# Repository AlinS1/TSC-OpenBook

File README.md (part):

# OpenBook Project - TSC
### Similea Alin-Andrei 334CA

## Diagrama

## Descriere functionalitate hardware
Dispozitivul are in centrul sau un microcontroler ESP32-C6 care interactioneaza cu
un display, un senzor de mediu, un RTC, un SD card si un circuit de gestionare a
alimentarii. Este un dispozitiv alimentat cu baterie, cu conectivitate USB-C.

In ceea ce priveste alimentarea dispozitivului, se foloseste conectorul USB-C
(SAMACSYS_PARTS_USB4110-GF-A) ce dispune de protectie ESD.
Are un controller de incarcare pentru baterii Li-Po(Li-Po Battery Charging
Controller - MCP73831) care se ocupa de incarcarea bateriei.
Mai exista si un stabilizator de tensiune LDO Voltage Regulator (XC6220A331MR-G)
ce asigura o alimentare stabila.
Nivelul de incarcare al bateriei este monitorizat cu ajutorul Battery Charge
Level (MAX17048G+T).

In ceea ce priveste memoria, este inclus un slot pentru card SD
(112A-TAAR-R03_ATTEND). In plus, avem o memorie Flash NOR externa (W25Q512JVIQ)
cu o capacitate de 64MB. Comunicarea cu acestea se face prin SPI (avem MOSI,
MISO, SS_SD si SCK).

Modulul DS3231SN RTC este responsabil pentru mentinerea timpului.
Comunicarea cu controller-ul se face prin I2C (deoarece avem SDA si SCL).
Dispozitivul are integrat si un senzor BME680, destinat analizei aerului,
masurarea presiunii atmosferice, temperaturii si umiditatii. Comunicare cu ESP32
se face tot prin I2C.
Este prezent o componenta Qwiic (QWIIC_CONNECTORJS-1MM) ce ne ajuta sa conectam
usor componente I2C intre ele. 

## Pini ESP32-C6
Modulul DS3231SN RTC foloseste pinii lui ESP32-C6 pentru SDA(19) si SCL(20),
deoarece comunica prin I2C. SDA e folosit pentru transferul de date, iar SCL
este linia de ceas folosita la sincronizare.

Senzorul de mediu BME680 foloseste aceiasi pini ca modulul RTC din aceleasi motive.

Cardul SD foloseste MOSI(7), MISO(27), SS_SD(4) si SCK(6), deoarece comunica prin SPI.

Display-ul E-Paper foloseste pini speciali ca EPD_3V3_C(18), EPD_CS(11), EPD_DC(5),
EPD_RST(21), EPD_BUSY(26).

Butoanele folosesc pinii RESET(3), IO/BOOT(15) si IO/CHANGE(23) pentru a realiza anumite actiuni.

## Rezolvare Erori/Warnings

De-alungul implementarii am avut urmatoarele probleme:
1. Bobina L1 - "Copper Width error" - a trebuit sa modific dimensiunile pad-urilor
din biblioteca data, deoarece nu erau conforme cu DRC-ul.

2. Componenta U4 - "Smd, -Net Class: 1 POWER Top" - Modificam dimensiunea smd-urilor
vizate la 32mil x 16mil.

3. Pentru ca traseele de alimentare sa aiba width (0.3mm) diferit de celelalte
(0.15mm) vom crea o regula custom pentru Copper Width folosind un net class separat
ce contine label-urile destinate traseelor de alimentare.

4. Pentru a ne asigura ca evitam vias-urile la traseele de putere, vom face prima
data rutarea acestora cu ajutorul liniei de comanda.
(auto 3V3 EPD_3V3 EPD_3V3_C VBUS VUSB VBAT VRTC)

## Bill Of Materials

| Schematic name | Value | Component | Footprint Name | Component link | Datasheet link |
|----------------|----------|----------------|----------------|----------------|----------------|		
|	BOOT_BUTTON	|	BUTTON_CUSYOMV1	|	BUTTON_CUSYOMV1	|	MYBUTTON	|	https://industry.panasonic.com/global/en/products/control/switch/light-touch/number/evqpuj02k	|	https://industry.panasonic.com/global/en/downloads?tab=catalog&small_g_cd=203&part_no=EVQPUJ02K	|
|	C1	|	100nF	|	ESP32_WROVER_EAGLE-LTSPICE_CC0402	|	ESP32_WROVER_EAGLE-LTSPICE_C0402	|	https://componentsearchengine.com/part-view/CC0402MRX5R5BB106/YAGEO	|	https://componentsearchengine.com/Datasheets/2/CC0402MRX5R5BB106.pdf	|
|	C1_BAT	|	4.7uF	|	ESP32_WROVER_EAGLE-LTSPICE_CC0402	|	ESP32_WROVER_EAGLE-LTSPICE_C0402	|	https://componentsearchengine.com/part-view/CC0402MRX5R5BB106/YAGEO	|	https://componentsearchengine.com/Datasheets/2/CC0402MRX5R5BB106.pdf	|
|	C1_BAT1	|	4.7uF	|	EAGLE-LTSPICE_CC0402	|	EAGLE-LTSPICE_C0402	|	https://www.snapeda.com/parts/CC0402DRNPO9BN5R1/Yageo/view-part/?ref=dk&t=LTSPICE_CC0402&con_ref=None	|	https://s3.amazonaws.com/snapeda/datasheet/CC0402DRNPO9BN5R1_Yageo.pdf	|
|	C2_BAT1	|	4.7uF	|	EAGLE-LTSPICE_CC0402	|	EAGLE-LTSPICE_C0402	|	https://www.snapeda.com/parts/CC0402DRNPO9BN5R1/Yageo/view-part/?ref=dk&t=LTSPICE_CC0402&con_ref=None	|	https://s3.amazonaws.com/snapeda/datasheet/CC0402DRNPO9BN5R1_Yageo.pdf	|
|	C1_BAT2	|	4.7uF	|	EAGLE-LTSPICE_CC0402	|	EAGLE-LTSPICE_C0402	|	https://www.snapeda.com/parts/CC0402DRNPO9BN5R1/Yageo/view-part/?ref=dk&t=LTSPICE_CC0402&con_ref=None	|	https://s3.amazonaws.com/snapeda/datasheet/CC0402DRNPO9BN5R1_Yageo.pdf	|
|	C2	|	100nF	|	ESP32_WROVER_EAGLE-LTSPICE_CC0402	|	ESP32_WROVER_EAGLE-LTSPICE_C0402	|	https://componentsearchengine.com/part-view/CC0402MRX5R5BB106/YAGEO	|	https://componentsearchengine.com/Datasheets/2/CC0402MRX5R5BB106.pdf	|
|	C2_BAT	|	4.7uF	|	ESP32_WROVER_EAGLE-LTSPICE_CC0402	|	ESP32_WROVER_EAGLE-LTSPICE_C0402	|	https://componentsearchengine.com/part-view/CC0402MRX5R5BB106/YAGEO	|	https://componentsearchengine.com/Datasheets/2/CC0402MRX5R5BB106.pdf	|
|	C3	|	100uF TANT	|	RCL_CPOL-EUCT3528	|	RCL_CT3528	|	https://www.snapeda.com/parts/TAJB475K025RNJ/AVX/view-part/?ref=dk&t=capacitor%203528&con_ref=None	|	https://s3.amazonaws.com/snapeda/datasheet/TAJB475K025RNJ_AVX.pdf	|
|	C4	|	4.7uF/25V	|	ESP32_WROVER_EAGLE-LTSPICE_CC0402	|	ESP32_WROVER_EAGLE-LTSPICE_C0402	|	https://componentsearchengine.com/part-view/CC0402MRX5R5BB106/YAGEO	|	https://componentsearchengine.com/Datasheets/2/CC0402MRX5R5BB106.pdf	|
|	C4_USB	|	100nF	|	ESP32_WROVER_EAGLE-LTSPICE_CC0402	|	ESP32_WROVER_EAGLE-LTSPICE_C0402	|	https://componentsearchengine.com/part-view/CC0402MRX5R5BB106/YAGEO	|	https://componentsearchengine.com/Datasheets/2/CC0402MRX5R5BB106.pdf	|
|	C5	|	1uF	|	ESP32_WROVER_EAGLE-LTSPICE_CC0402	|	ESP32_WROVER_EAGLE-LTSPICE_C0402	|	https://componentsearchengine.com/part-view/CC0402MRX5R5BB106/YAGEO	|	https://componentsearchengine.com/Datasheets/2/CC0402MRX5R5BB106.pdf	|
|	C5_USB	|	4.7uF	|	ESP32_WROVER_EAGLE-LTSPICE_CC0402	|	ESP32_WROVER_EAGLE-LTSPICE_C0402	|	https://componentsearchengine.com/part-view/CC0402MRX5R5BB106/YAGEO	|	https://componentsearchengine.com/Datasheets/2/CC0402MRX5R5BB106.pdf	|
|	C6	|	100nF	|	ESP32_WROVER_EAGLE-LTSPICE_CC0402	|	ESP32_WROVER_EAGLE-LTSPICE_C0402	|	https://componentsearchengine.com/part-view/CC0402MRX5R5BB106/YAGEO	|	https://componentsearchengine.com/Datasheets/2/CC0402MRX5R5BB106.pdf	|
|	C7	|	10uF	|	ESP32_WROVER_EAGLE-LTSPICE_CC0402	|	ESP32_WROVER_EAGLE-LTSPICE_C0402	|	https://componentsearchengine.com/part-view/CC0402MRX5R5BB106/YAGEO	|	https://componentsearchengine.com/Datasheets/2/CC0402MRX5R5BB106.pdf	|
|	C8	|	100nF	|	ESP32_WROVER_EAGLE-LTSPICE_CC0402	|	ESP32_WROVER_EAGLE-LTSPICE_C0402	|	https://componentsearchengine.com/part-view/CC0402MRX5R5BB106/YAGEO	|	https://componentsearchengine.com/Datasheets/2/CC0402MRX5R5BB106.pdf	|
|	C9	|	100nF	|	EAGLE-LTSPICE_CC0402	|	EAGLE-LTSPICE_C0402	|	https://www.snapeda.com/parts/CC0402DRNPO9BN5R1/Yageo/view-part/?ref=dk&t=LTSPICE_CC0402&con_ref=None	|	https://s3.amazonaws.com/snapeda/datasheet/CC0402DRNPO9BN5R1_Yageo.pdf	|
|	C10	|	100nF	|	ESP32_WROVER_EAGLE-LTSPICE_CC0402	|	ESP32_WROVER_EAGLE-LTSPICE_C0402	|	https://componentsearchengine.com/part-view/CC0402MRX5R5BB106/YAGEO	|	https://componentsearchengine.com/Datasheets/2/CC0402MRX5R5BB106.pdf	|
|	C10_SUPERCAP	|	CPH3225A	|	CPH3225A	|	CAPCP3225X100N	|	https://www.snapeda.com/parts/CPH3225A/Seiko+Instruments/view-part/?ref=eda	|	https://www.snapeda.com/parts/CPH3225A/Seiko%20Instruments/datasheet/	|
|	CHANGE_BUTTON	|	BUTTON_CUSYOMV1	|	BUTTON_CUSYOMV1	|	MYBUTTON	|	https://industry.panasonic.com/global/en/products/control/switch/light-touch/number/evqpuj02k	|	https://industry.panasonic.com/global/en/downloads?tab=catalog&small_g_cd=203&part_no=EVQPUJ02K	|
|	CHG_LED	|		|	ADAFRUIT_LEDCHIP-LED0603	|	ADAFRUIT_CHIP-LED0603	|	https://www.snapeda.com/parts/KP-1608SURCK/Kingbright/view-part/?ref=search&t=LED%200603	|	https://www.snapeda.com/parts/KP-1608SURCK/Kingbright/datasheet/	|
|	C_DELAY	|	100nF	|	ESP32_WROVER_EAGLE-LTSPICE_CC0402	|	ESP32_WROVER_EAGLE-LTSPICE_C0402	|	https://componentsearchengine.com/part-view/CC0402MRX5R5BB106/YAGEO	|	https://componentsearchengine.com/Datasheets/2/CC0402MRX5R5BB106.pdf	|
|	D1	|	USBLC6-2SC6Y	|	USBLC6-2SC6Y	|	SOT95P280X145-6N	|	https://www.snapeda.com/parts/USBLC6-2SC6Y/STMicroelectronics/view-part/?ref=snap	|	https://www.snapeda.com/parts/USBLC6-2SC6Y/STMicroelectronics/datasheet/	|
|	D2	|	ESP32_WROVER_AVX---SD0805S020S1R0_AVX_SD0805S020S1R0_0_0AVX_SD0805S020S1R0_0_0	|	ESP32_WROVER_AVX---SD0805S020S1R0_AVX_SD0805S020S1R0_0_0AVX_SD0805S020S1R0_0_0	|	ESP32_WROVER_AVX---SD0805S020S1R0_AVX_SD0805S020S1R0_0	|	https://ro.mouser.com/ProductDetail/KYOCERA-AVX/SD0805S020S1R0?qs=jCA%252BPfw4LHbpkAoSnwrdjw%3D%3D	|	http://datasheets.avx.com/schottky.pdf	|
|	D3	|	MBR0530	|	MBR0530	|	SOD3716X135N	|	https://www.snapeda.com/parts/MBR0530/Onsemi/view-part/?ref=eda	|	https://www.snapeda.com/parts/MBR0530/ON%20Semiconductor/datasheet/	|
|	D4	|	MBR0530	|	MBR0530	|	SOD3716X135N	|	https://www.snapeda.com/parts/MBR0530/Onsemi/view-part/?ref=eda	|	https://www.snapeda.com/parts/MBR0530/ON%20Semiconductor/datasheet/	|
|	D5	|	MBR0530	|	MBR0530	|	SOD3716X135N	|	https://www.snapeda.com/parts/MBR0530/Onsemi/view-part/?ref=eda	|	https://www.snapeda.com/parts/MBR0530/ON%20Semiconductor/datasheet/	|
|	D6	|	PGB1010603MR	|	PGB1010603MR	|	DIOC1608X36N	|	https://www.snapeda.com/parts/PGB1010603MR/Littelfuse/view-part/?ref=eda	|	https://www.snapeda.com/parts/PGB1010603MR/Littelfuse%20Inc./datasheet/	|
|	D7	|	ESP32_WROVER_AVX---SD0805S020S1R0_AVX_SD0805S020S1R0_0_0AVX_SD0805S020S1R0_0_0	|	ESP32_WROVER_AVX---SD0805S020S1R0_AVX_SD0805S020S1R0_0_0AVX_SD0805S020S1R0_0_0	|	ESP32_WROVER_AVX---SD0805S020S1R0_AVX_SD0805S020S1R0_0	|	https://eu.mouser.com/ProductDetail/KYOCERA-AVX/SD0805S020S1R0?qs=jCA%252BPfw4LHbpkAoSnwrdjw%3D%3D	|	http://datasheets.avx.com/schottky.pdf	|
|	D8	|	PGB1010603MR	|	PGB1010603MR	|	DIOC1608X36N	|	https://www.snapeda.com/parts/PGB1010603MR/Littelfuse/view-part/?ref=eda	|	https://www.snapeda.com/parts/PGB1010603MR/Littelfuse%20Inc./datasheet/	|
|	D9	|	PGB1010603MR	|	PGB1010603MR	|	DIOC1608X36N	|	https://www.snapeda.com/parts/PGB1010603MR/Littelfuse/view-part/?ref=eda	|	https://www.snapeda.com/parts/PGB1010603MR/Littelfuse%20Inc./datasheet/	|
|	D10	|	PGB1010603MR	|	PGB1010603MR	|	DIOC1608X36N	|	https://www.snapeda.com/parts/PGB1010603MR/Littelfuse/view-part/?ref=eda	|	https://www.snapeda.com/parts/PGB1010603MR/Littelfuse%20Inc./datasheet/	|
|	D11	|	PGB1010603MR	|	PGB1010603MR	|	DIOC1608X36N	|	https://www.snapeda.com/parts/PGB1010603MR/Littelfuse/view-part/?ref=eda	|	https://www.snapeda.com/parts/PGB1010603MR/Littelfuse%20Inc./datasheet/	|
|	D12	|	PGB1010603MR	|	PGB1010603MR	|	DIOC1608X36N	|	https://www.snapeda.com/parts/PGB1010603MR/Littelfuse/view-part/?ref=eda	|	https://www.snapeda.com/parts/PGB1010603MR/Littelfuse%20Inc./datasheet/	|
|	EPD_C1	|	1uF/50V	|	ESP32_WROVER_EAGLE-LTSPICE_CC0402	|	ESP32_WROVER_EAGLE-LTSPICE_C0402	|	https://componentsearchengine.com/part-view/CC0402MRX5R5BB106/YAGEO	|	https://componentsearchengine.com/Datasheets/2/CC0402MRX5R5BB106.pdf	|
|	EPD_C2	|	1uF/50V	|	ESP32_WROVER_EAGLE-LTSPICE_CC0402	|	ESP32_WROVER_EAGLE-LTSPICE_C0402	|	https://componentsearchengine.com/part-view/CC0402MRX5R5BB106/YAGEO	|	https://componentsearchengine.com/Datasheets/2/CC0402MRX5R5BB106.pdf	|
|	EPD_C5	|	1uF/50V	|	ESP32_WROVER_EAGLE-LTSPICE_CC0402	|	ESP32_WROVER_EAGLE-LTSPICE_C0402	|	https://componentsearchengine.com/part-view/CC0402MRX5R5BB106/YAGEO	|	https://componentsearchengine.com/Datasheets/2/CC0402MRX5R5BB106.pdf	|
|	EPD_C6	|	1uF/50V	|	ESP32_WROVER_EAGLE-LTSPICE_CC0402	|	ESP32_WROVER_EAGLE-LTSPICE_C0402	|	https://componentsearchengine.com/part-view/CC0402MRX5R5BB106/YAGEO	|	https://componentsearchengine.com/Datasheets/2/CC0402MRX5R5BB106.pdf	|
|	EPD_C7	|	1uF/50V	|	ESP32_WROVER_EAGLE-LTSPICE_CC0402	|	ESP32_WROVER_EAGLE-LTSPICE_C0402	|	https://componentsearchengine.com/part-view/CC0402MRX5R5BB106/YAGEO	|	https://componentsearchengine.com/Datasheets/2/CC0402MRX5R5BB106.pdf	|
|	EPD_C8	|	1uF/50V	|	ESP32_WROVER_EAGLE-LTSPICE_CC0402	|	ESP32_WROVER_EAGLE-LTSPICE_C0402	|	https://componentsearchengine.com/part-view/CC0402MRX5R5BB106/YAGEO	|	https://componentsearchengine.com/Datasheets/2/CC0402MRX5R5BB106.pdf	|
|	EPD_C9	|	1uF/50V	|	ESP32_WROVER_EAGLE-LTSPICE_CC0402	|	ESP32_WROVER_EAGLE-LTSPICE_C0402	|	https://componentsearchengine.com/part-view/CC0402MRX5R5BB106/YAGEO	|	https://componentsearchengine.com/Datasheets/2/CC0402MRX5R5BB106.pdf	|
|	EPD_C10	|	1uF/50V	|	ESP32_WROVER_EAGLE-LTSPICE_CC0402	|	ESP32_WROVER_EAGLE-LTSPICE_C0402	|	https://componentsearchengine.com/part-view/CC0402MRX5R5BB106/YAGEO	|	https://componentsearchengine.com/Datasheets/2/CC0402MRX5R5BB106.pdf	|
|	EPD_C11	|	1uF/50V	|	ESP32_WROVER_EAGLE-LTSPICE_CC0402	|	ESP32_WROVER_EAGLE-LTSPICE_C0402	|	https://componentsearchengine.com/part-view/CC0402MRX5R5BB106/YAGEO	|	https://componentsearchengine.com/Datasheets/2/CC0402MRX5R5BB106.pdf	|
|	EPD_C12	|	1uF/50V	|	ESP32_WROVER_EAGLE-LTSPICE_CC0402	|	ESP32_WROVER_EAGLE-LTSPICE_C0402	|	https://componentsearchengine.com/part-view/CC0402MRX5R5BB106/YAGEO	|	https://componentsearchengine.com/Datasheets/2/CC0402MRX5R5BB106.pdf	|
|	IC1	|	BD5229G-TR	|	BD5229G-TR	|	SOT95P280X125-5N	|	https://componentsearchengine.com/part-view/BD5229G-TR/ROHM%20Semiconductor	|	https://datasheet.datasheetarchive.com/originals/distributors/Datasheets_SAMA/f2b9741ef86007909f138d561a359946.pdf	|
|	IC4	|	XC6220A331MR-G	|	XC6220A331MR-G	|	SOT95P280X120-5N	|	https://componentsearchengine.com/part-view/XC6220A331MR-G/Torex	|	https://product.torexsemi.com/system/files/series/xc6220.pdf	|
|	J1	|	FH34SRJ-24S-0.5SH_99_	|	FH34SRJ-24S-0.5SH_99_	|	FH34SRJ24S05SH99	|	https://componentsearchengine.com/part-view/FH34SRJ-24S-0.5SH(99)/Hirose	|	https://www.hirose.com/en/product/document?clcode=CL0580-1255-6-99&productname=FH34SRJ-24S-0.5SH(99)&series=FH34SRJ&documenttype=2DDrawing&lang=en&documentid=0000990903	|
|	J2	|	SAMACSYS_PARTS_USB4110-GF-A	|	SAMACSYS_PARTS_USB4110-GF-A	|	SAMACSYS_PARTS_USB4110GFA	|	https://componentsearchengine.com/part-view/USB4110-GF-A/GCT%20(GLOBAL%20CONNECTOR%20TECHNOLOGY)	|	https://gct.co/files/drawings/usb4110.pdf	|
|	J3	|	QWIIC_RIGHT_ANGLE	|	QWIIC_CONNECTORJS-1MM	|	JST04_1MM_RA	|	https://grabcad.com/library/sparkfun-qwiic-right-angle-1	|	https://eu.mouser.com/ProductDetail/Adafruit/4208?qs=PzGy0jfpSMtbScLbr0L5dw%3D%3D	|
|	J4	|	112A-TAAR-R03_ATTEND	|	112A-TAAR-R03_ATTEND	|	112ATAARR03ATTEND	|	https://store.comet.srl.ro/Catalogue/Product/43497/	|	https://store.comet.srl.ro/Catalogue/Product/43497/	|
|	L1	|	68uH	|	744043680IND_4828-WE-TPC_WRE	|	IND_4828-WE-TPC_WRE	|	https://ro.mouser.com/ProductDetail/Wurth-Elektronik/744043680?qs=PGXP4M47uW6VkZq%252BkzjrHA%3D%3D	|	https://www.we-online.com/components/products/datasheet/744043680.pdf	|
|	PFMF.050.1	|	ESP32C6_VARISTORCN1812	|	ESP32C6_VARISTORCN1812	|	ESP32C6_VARISTOR_CT/CN1812	|	https://www.mouser.co.uk/ProductDetail/EPCOS-TDK/B72520T0350K062?qs=dEfas%2FXlABIszF52uu7vrg%3D%3D	|	https://www.mouser.co.uk/ProductDetail/EPCOS-TDK/B72520T0350K062?qs=dEfas%2FXlABIszF52uu7vrg%3D%3D	|
|	Q1	|	20V/4.2A/52mO/1.4W	|	ESP32_WROVER_SPARKFUN-DISCRETESEMI_MOSFET_PCH-DMG2305UX-7	|	ESP32_WROVER_SPARKFUN-DISCRETESEMI_SOT23-3	|	https://componentsearchengine.com/part-view/DMG2305UX-7/Diodes%20Incorporated	|	https://www.diodes.com//assets/Datasheets/DMG2305UX.pdf	|
|	Q2	|	20V/4.2A/52mO/1.4W	|	ESP32_WROVER_SPARKFUN-DISCRETESEMI_MOSFET_PCH-DMG2305UX-7	|	ESP32_WROVER_SPARKFUN-DISCRETESEMI_SOT23-3	|	https://componentsearchengine.com/part-view/DMG2305UX-7/Diodes%20Incorporated	|	https://www.diodes.com//assets/Datasheets/DMG2305UX.pdf	|
|	Q3	|	SI1308EDL-T1-GE3	|	D8	|	SOT65P210X110-3N	|	https://componentsearchengine.com/part-view/SI1308EDL-T1-GE3/Vishay	|	https://componentsearchengine.com/Datasheets/1/SI1308EDL-T1-GE3.pdf	|
|	R1	|	10K	|	ESP32_WROVER_EAGLE-LTSPICE_RR0402	|	ESP32_WROVER_EAGLE-LTSPICE_R0402	|	https://componentsearchengine.com/part-view/R0402%201%25%20100%20K%20(RC0402FR-07100KL)/YAGEO	|	https://www.yageo.com/upload/media/product/products/datasheet/rchip/PYu-RC_Group_51_RoHS_L_12.pdf	|
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
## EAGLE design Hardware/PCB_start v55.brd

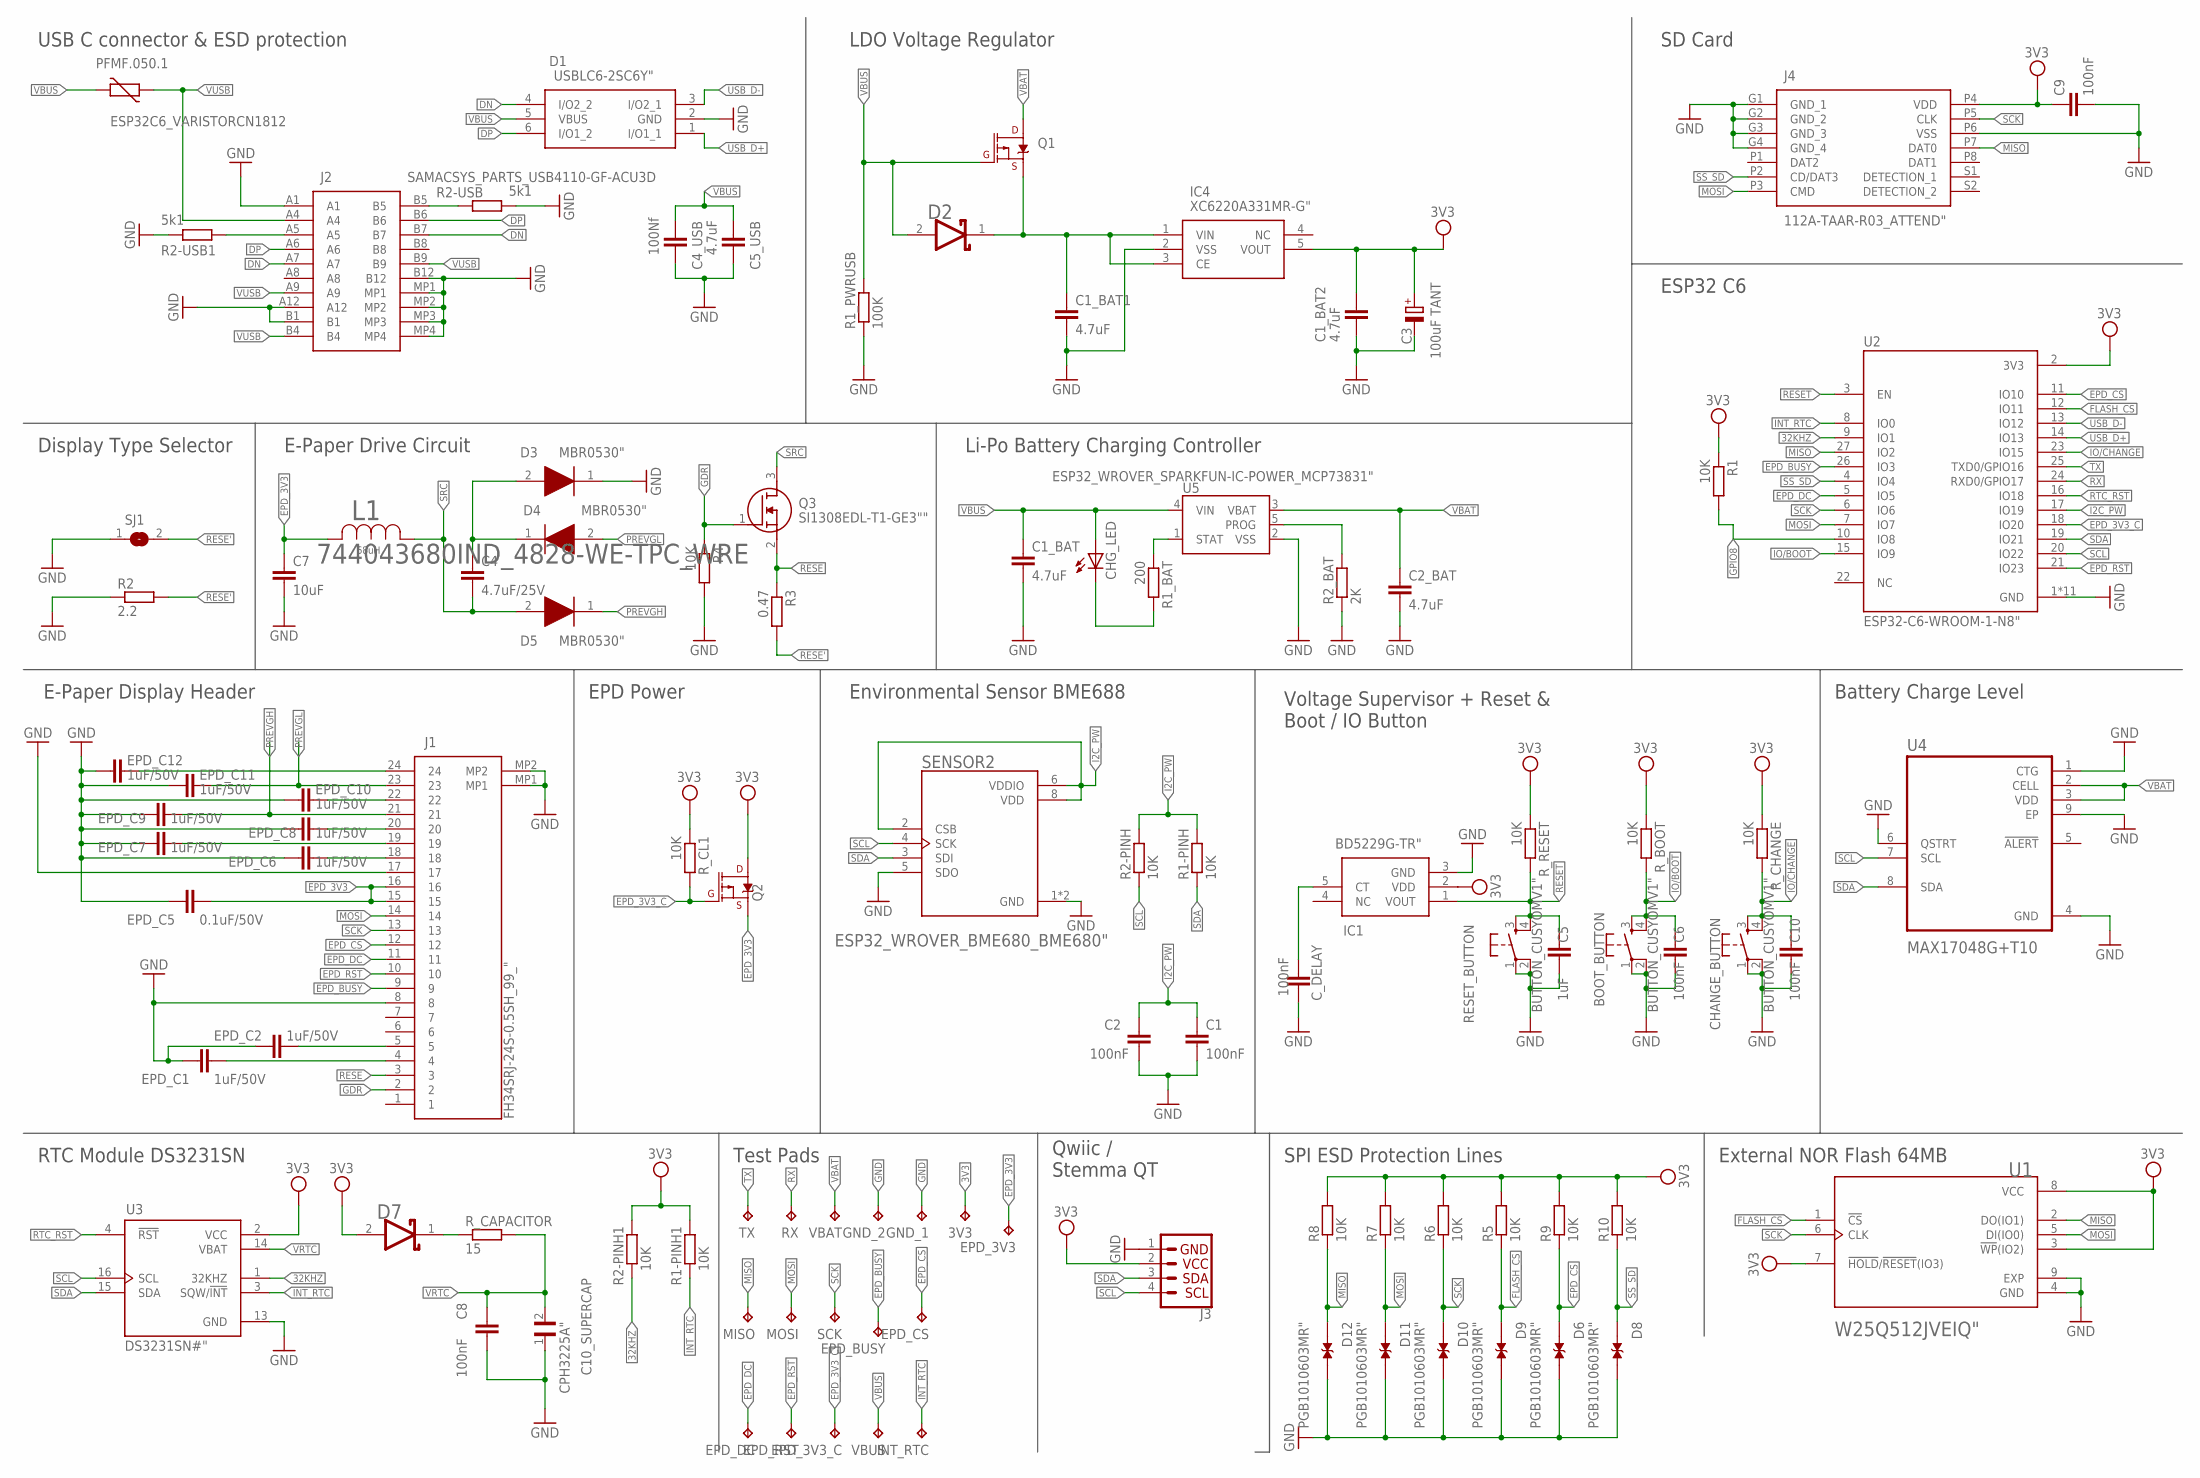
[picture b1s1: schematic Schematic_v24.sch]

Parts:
3V3: TPTP20R; TP20R
BOOT_BUTTON: BUTTON_CUSYOMV1"; MYBUTTON
C1, C2, C6, C8, C10: 100nF; ESP32_WROVER_EAGLE-LTSPICE_C0402
C1_BAT, C2_BAT, C5_USB: 4.7uF; ESP32_WROVER_EAGLE-LTSPICE_C0402
C1_BAT1, C1_BAT2: 4.7uF; EAGLE-LTSPICE_C0402
C3: 100uF TANT; RCL_CT3528
C4: 4.7uF/25V; ESP32_WROVER_EAGLE-LTSPICE_C0402
C4_USB: 100Nf; ESP32_WROVER_EAGLE-LTSPICE_C0402
C5: 1uF; ESP32_WROVER_EAGLE-LTSPICE_C0402
C7: 10uF; ESP32_WROVER_EAGLE-LTSPICE_C0402
C9: 100nF; EAGLE-LTSPICE_C0402
C10_SUPERCAP: CPH3225A"; CAPCP3225X100N
CHANGE_BUTTON: BUTTON_CUSYOMV1"; MYBUTTON
CHG_LED: ADAFRUIT_LEDCHIP-LED0603; ADAFRUIT_CHIP-LED0603
C_DELAY: 100nF; ESP32_WROVER_EAGLE-LTSPICE_C0402
D1: USBLC6-2SC6Y"; SOT95P280X145-6N
D2, D7: ESP32_WROVER_AVX---SD0805S020S1R0_AVX_SD0805S020S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; ESP32_WROVER_AVX---SD0805S020S1R0_AVX_SD0805S020S1R0_0
D3, D4, D5: MBR0530"; SOD3716X135N
D6, D8, D9, D10, D11, D12: PGB1010603MR"; DIOC1608X36N
EPD_3V3, EPD_3V3_C: TPTP20R; TP20R
EPD_BUSY: TPTP20R; TP20R
EPD_C1, EPD_C2, EPD_C6, EPD_C7, EPD_C8, EPD_C9, EPD_C10, EPD_C11, EPD_C12: 1uF/50V; ESP32_WROVER_EAGLE-LTSPICE_C0402
EPD_C5: 0.1uF/50V; ESP32_WROVER_EAGLE-LTSPICE_C0402
EPD_CS: TPTP20R; TP20R
EPD_DC: TPTP20R; TP20R
EPD_RST: TPTP20R; TP20R
GND_1, GND_2: TPTP20R; TP20R
IC1: BD5229G-TR"; SOT95P280X125-5N
IC4: XC6220A331MR-G"; SOT95P280X120-5N
INT_RTC: TPTP20R; TP20R
J1: FH34SRJ-24S-0.5SH_99_"; FH34SRJ24S05SH99
J2: SAMACSYS_PARTS_USB4110-GF-ACU3D; SAMACSYS_PARTS_USB4110GFA
J3: QWIIC_RIGHT_ANGLE; JST04_1MM_RA
J4: 112A-TAAR-R03_ATTEND"; 112ATAARR03ATTEND
L1: 744043680IND_4828-WE-TPC_WRE; IND_4828-WE-TPC_WRE
MISO: TPTP20R; TP20R
MOSI: TPTP20R; TP20R
PFMF.050.1: ESP32C6_VARISTORCN1812; ESP32C6_VARISTOR_CT/CN1812
Q1, Q2: 20V/4.2A/52mΩ/1.4W; ESP32_WROVER_SPARKFUN-DISCRETESEMI_SOT23-3
Q3: SI1308EDL-T1-GE3""; SOT65P210X110-3N
R1, R1-PINH, R1-PINH1, R2-PINH, R2-PINH1, R4, R5, R6, R7, R8, R9, R10: 10K; ESP32_WROVER_EAGLE-LTSPICE_R0402
R1_BAT: 200; ESP32_WROVER_EAGLE-LTSPICE_R0402
R1_PWRUSB: 100K; ESP32_WROVER_EAGLE-LTSPICE_R0402
R2: 2.2; ESP32_WROVER_EAGLE-LTSPICE_R0402
R2-USB, R2-USB1: 5k1; ESP32_WROVER_EAGLE-LTSPICE_R0402
R2_BAT: 2K; ESP32_WROVER_EAGLE-LTSPICE_R0402
R3: 0.47; ESP32_WROVER_EAGLE-LTSPICE_R0402
RESET_BUTTON: BUTTON_CUSYOMV1"; MYBUTTON
RX: TPTP20R; TP20R
R_BOOT: 10K; ESP32_WROVER_EAGLE-LTSPICE_R0402
R_CAPACITOR: 15; ESP32_WROVER_EAGLE-LTSPICE_R0402
R_CHANGE: 10K; ESP32_WROVER_EAGLE-LTSPICE_R0402
R_CL1: 10K; ESP32_WROVER_EAGLE-LTSPICE_R0402
R_RESET: 10K; ESP32_WROVER_EAGLE-LTSPICE_R0402
SCK: TPTP20R; TP20R
SENSOR2: ESP32_WROVER_BME680_BME680"; ESP32_WROVER_BME680_PSON80P300X300X100-8N
SJ1: SJ""; SJ
TX: TPTP20R; TP20R
U1: W25Q512JVEIQ"; SON127P600X800X80-9N
U2: ESP32-C6-WROOM-1-N8"; XCVR_ESP32-C6-WROOM-1-N8
U3: DS3231SN#"; SOIC127P1032X265-16N
U4: MAX17048G+T10; SON50P200X200X80-9N
U5: ESP32_WROVER_SPARKFUN-IC-POWER_MCP73831"; ESP32_WROVER_SPARKFUN-IC-POWER_SOT23-5
VBAT: TPTP20R; TP20R
VBUS: TPTP20R; TP20R

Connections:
3V3: 3V3.TP, C1_BAT2.1, C3.+, C9.1, D7.2 (ANODE), IC1.2 (VDD), IC4.5 (VOUT), J3.2, J4.P4 (VDD), Q2.3 (D), R1.1, R1-PINH1.2, R2-PINH1.2, R5.2, R6.2, R7.2, R8.2, R9.2, R10.2, R_BOOT.1, R_CHANGE.1, R_CL1.1, R_RESET.1, U1.3 (!WP!(IO2)), U1.7 (!HOLD!/!RESET!(IO3)), U1.8 (VCC), U2.2 (3V3), U3.2 (VCC)
32KHZ: R2-PINH1.1, U2.9 (IO1), U3.1 (32KHZ)
DN: D1.4 (I/O2_2), J2.A7, J2.B7
DP: D1.6 (I/O1_2), J2.A6, J2.B6
EPD_3V3: C7.1, EPD_3V3.TP, EPD_C5.1, J1.15, J1.16, L1.2, Q2.2 (S)
EPD_3V3_C: EPD_3V3_C.TP, Q2.1 (G), R_CL1.2, U2.18 (IO20)
EPD_BUSY: EPD_BUSY.TP, J1.9, U2.26 (IO3)
EPD_CS: D6.1, EPD_CS.TP, J1.12, R9.1, U2.11 (IO10)
EPD_DC: EPD_DC.TP, J1.11, U2.5 (IO5)
EPD_RST: EPD_RST.TP, J1.10, U2.21 (IO23)
FLASH_CS: D9.1, R5.1, U1.1 (!CS), U2.12 (IO11)
GDR: J1.2, Q3.1 (G), R4.1
GND: BOOT_BUTTON.1, BOOT_BUTTON.2, C1.2, C1_BAT.2, C1_BAT1.2, C1_BAT2.2, C2.2, C2_BAT.2, C3.-, C4_USB.2, C5.2, C5_USB.2, C6.2, C7.2, C8.2, C9.2, C10.2, C10_SUPERCAP.1, CHANGE_BUTTON.1, CHANGE_BUTTON.2, C_DELAY.2, D1.2 (GND), D3.1 (K), D6.2, D8.2, D9.2, D10.2, D11.2, D12.2, EPD_C1.2, EPD_C2.2, EPD_C5.2, EPD_C6.2, EPD_C7.2, EPD_C8.2, EPD_C9.2, EPD_C10.2, EPD_C11.2, EPD_C12.2, GND_1.TP, GND_2.TP, IC1.3 (GND), IC4.2 (VSS), J1.8, J1.17, J1.MP1, J1.MP2, J2.A1, J2.A12, J2.B1, J2.B12, J2.MP1, J2.MP2, J2.MP3, J2.MP4, J3.1, J4.G1 (GND_1), J4.G2 (GND_2), J4.G3 (GND_3), J4.G4 (GND_4), J4.P6 (VSS), R1_PWRUSB.1, R2.1, R2-USB.2, R2-USB1.1, R2_BAT.1, R4.2, RESET_BUTTON.1, RESET_BUTTON.2, SENSOR2.1 (GND), SENSOR2.5 (SDO), SENSOR2.7 (GND), SJ1.1, U1.4 (GND), U1.9 (EXP), U2.1 (GND), U2.28 (GND), U2.29_1 (GND), U2.29_2 (GND), U2.29_3 (GND), U2.29_4 (GND), U2.29_5 (GND), U2.29_6 (GND), U2.29_7 (GND), U2.29_8 (GND), U2.29_9 (GND), U3.13 (GND), U4.1 (CTG), U4.4 (GND), U4.6 (QSTRT), U4.9 (EP), U5.2 (VSS)
GPIO8: R1.2, U2.10 (IO8)
I2C_PW: C1.1, C2.1, R1-PINH.2, R2-PINH.2, SENSOR2.2 (CSB), SENSOR2.6 (VDDIO), SENSOR2.8 (VDD), U2.17 (IO19)
INT_RTC: INT_RTC.TP, R1-PINH1.1, U2.8 (IO0), U3.3 (SQW/!INT)
IO/BOOT: BOOT_BUTTON.3, BOOT_BUTTON.4, C6.1, R_BOOT.2, U2.15 (IO9)
IO/CHANGE: C10.1, CHANGE_BUTTON.3, CHANGE_BUTTON.4, R_CHANGE.2, U2.23 (IO15)
MISO: D12.1, J4.P7 (DAT0), MISO.TP, R8.1, U1.2 (DO(IO1)), U2.27 (IO2)
MOSI: D11.1, J1.14, J4.P3 (CMD), MOSI.TP, R7.1, U1.5 (DI(IO0)), U2.7 (IO7)
unnamed: C1_BAT1.1, D2.1 (CATHODE), IC4.1 (VIN), IC4.3 (CE), Q1.2 (S)
unnamed: C_DELAY.1, IC1.5 (CT)
unnamed: J2.B5, R2-USB.1
unnamed: J2.A5, R2-USB1.2
unnamed: R1_BAT.1, U5.1 (STAT)
unnamed: CHG_LED.C, R1_BAT.2
unnamed: C4.1, D3.2 (A), D4.1 (K)
unnamed: R2_BAT.2, U5.5 (PROG)
unnamed: EPD_C1.1, J1.4
unnamed: EPD_C2.1, J1.5
unnamed: D7.1 (CATHODE), R_CAPACITOR.1
unnamed: EPD_C6.1, J1.18
unnamed: EPD_C7.1, J1.19
unnamed: EPD_C8.1, J1.20
unnamed: EPD_C10.1, J1.22
unnamed: EPD_C12.1, J1.24
PREVGH: D5.1 (K), EPD_C9.1, J1.21
PREVGL: D4.2 (A), EPD_C11.1, J1.23
RESE: J1.3, Q3.2 (S), R3.1
RESE': R2.2, R3.2, SJ1.2
RESET: C5.1, IC1.1 (VOUT), RESET_BUTTON.3, RESET_BUTTON.4, R_RESET.2, U2.3 (EN)
RTC_RST: U2.16 (IO18), U3.4 (!RST)
RX: RX.TP, U2.24 (RXD0/GPIO17)
SCK: D10.1, J1.13, J4.P5 (CLK), R6.1, SCK.TP, U1.6 (CLK), U2.6 (IO6)
SCL: J3.4, R2-PINH.1, SENSOR2.4 (SCK), U2.20 (IO22), U3.16 (SCL), U4.7 (SCL)
SDA: J3.3, R1-PINH.1, SENSOR2.3 (SDI), U2.19 (IO21), U3.15 (SDA), U4.8 (SDA)
SRC: C4.2, D5.2 (A), L1.1, Q3.3 (D)
SS_SD: D8.1, J4.P2 (CD/DAT3), R10.1, U2.4 (IO4)
TX: TX.TP, U2.25 (TXD0/GPIO16)
USB_D+: D1.1 (I/O1_1), U2.14 (IO13)
USB_D-: D1.3 (I/O2_1), U2.13 (IO12)
VBAT: C2_BAT.1, Q1.3 (D), U4.2 (CELL), U4.3 (VDD), U5.3 (VBAT), VBAT.TP
VBUS: C1_BAT.1, C4_USB.1, C5_USB.1, CHG_LED.A, D1.5 (VBUS), D2.2 (ANODE), PFMF.050.1.2, Q1.1 (G), R1_PWRUSB.2, U5.4 (VIN), VBUS.TP
VRTC: C8.1, C10_SUPERCAP.2, R_CAPACITOR.2, U3.14 (VBAT)
VUSB: J2.A4, J2.A9, J2.B4, J2.B9, PFMF.050.1.1

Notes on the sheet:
USB C connector & ESD protection
LDO Voltage Regulator
SD Card
ESP32 C6
Li-Po Battery Charging Controller
E-Paper Drive Circuit
Display Type Selector
E-Paper Display Header
EPD Power
Environmental Sensor BME688
Voltage Supervisor + Reset & Boot / IO Button
Battery Charge Level
RTC Module DS3231SN
Test Pads
Qwiic / Stemma QT
SPI ESD Protection Lines
External NOR Flash 64MB

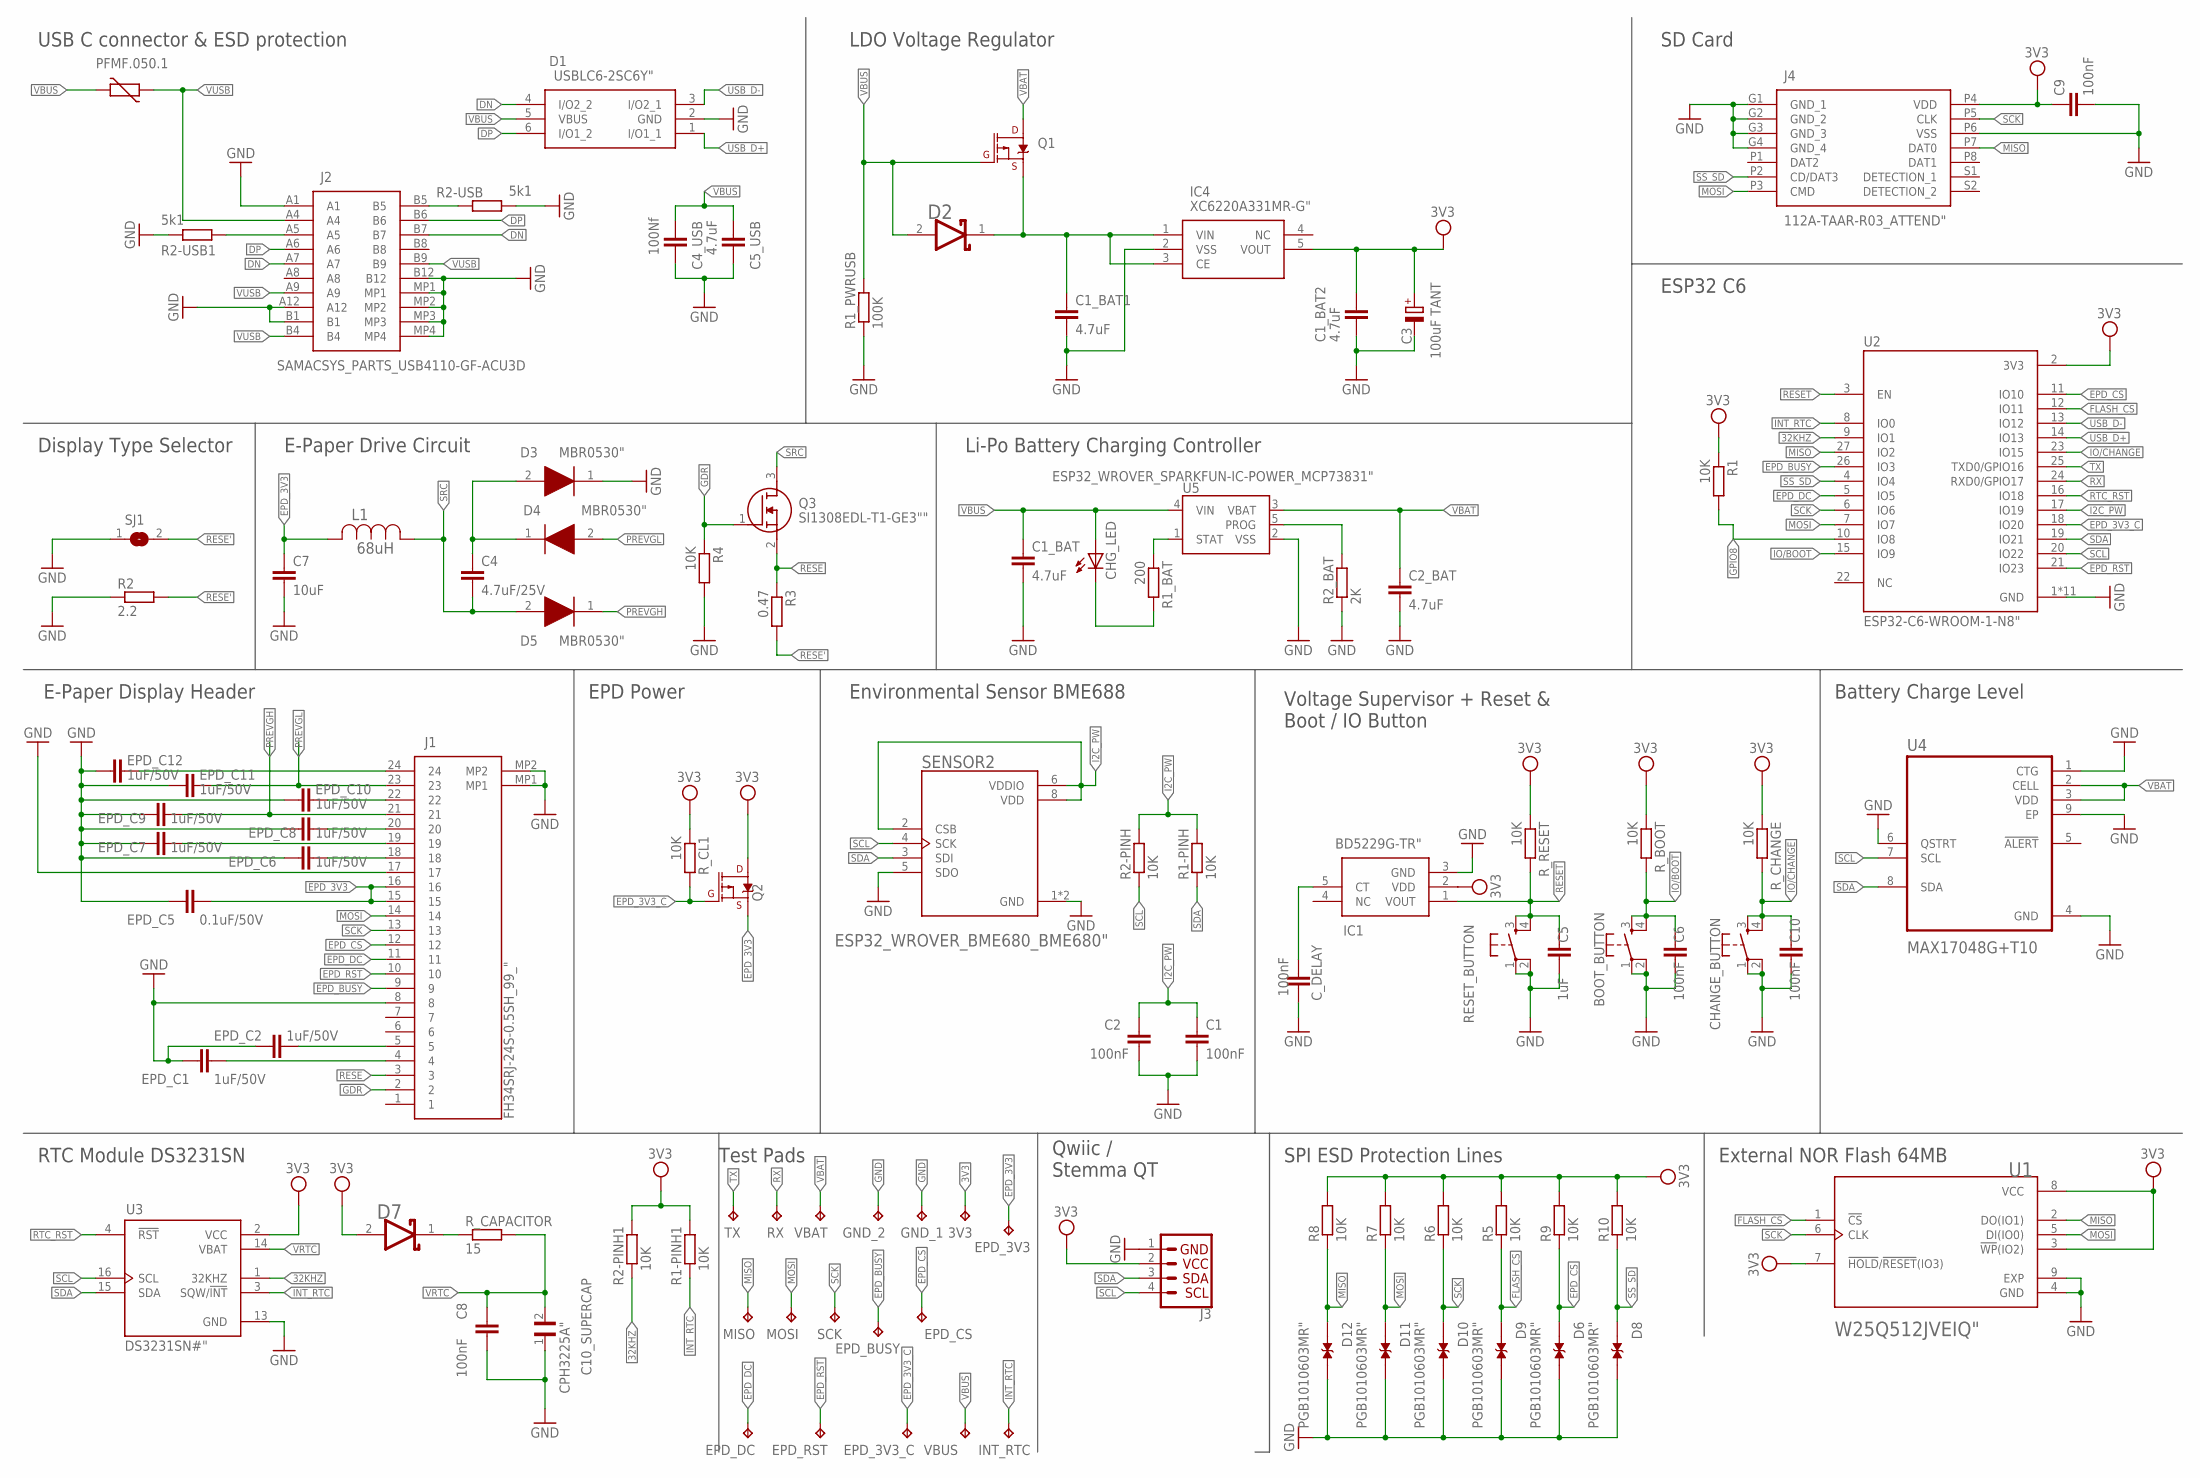
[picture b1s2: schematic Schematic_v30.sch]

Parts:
3V3: TPTP20R; TP20R
BOOT_BUTTON: BUTTON_CUSYOMV1"; MYBUTTON
C1, C2, C6, C8, C10: 100nF; ESP32_WROVER_EAGLE-LTSPICE_C0402
C1_BAT, C2_BAT, C5_USB: 4.7uF; ESP32_WROVER_EAGLE-LTSPICE_C0402
C1_BAT1, C1_BAT2: 4.7uF; EAGLE-LTSPICE_C0402
C3: 100uF TANT; RCL_CT3528
C4: 4.7uF/25V; ESP32_WROVER_EAGLE-LTSPICE_C0402
C4_USB: 100Nf; ESP32_WROVER_EAGLE-LTSPICE_C0402
C5: 1uF; ESP32_WROVER_EAGLE-LTSPICE_C0402
C7: 10uF; ESP32_WROVER_EAGLE-LTSPICE_C0402
C9: 100nF; EAGLE-LTSPICE_C0402
C10_SUPERCAP: CPH3225A"; CAPCP3225X100N
CHANGE_BUTTON: BUTTON_CUSYOMV1"; MYBUTTON
CHG_LED: ADAFRUIT_LEDCHIP-LED0603; ADAFRUIT_CHIP-LED0603
C_DELAY: 100nF; ESP32_WROVER_EAGLE-LTSPICE_C0402
D1: USBLC6-2SC6Y"; SOT95P280X145-6N
D2, D7: ESP32_WROVER_AVX---SD0805S020S1R0_AVX_SD0805S020S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; ESP32_WROVER_AVX---SD0805S020S1R0_AVX_SD0805S020S1R0_0
D3, D4, D5: MBR0530"; SOD3716X135N
D6, D8, D9, D10, D11, D12: PGB1010603MR"; DIOC1608X36N
EPD_3V3, EPD_3V3_C: TPTP20R; TP20R
EPD_BUSY: TPTP20R; TP20R
EPD_C1, EPD_C2, EPD_C6, EPD_C7, EPD_C8, EPD_C9, EPD_C10, EPD_C11, EPD_C12: 1uF/50V; ESP32_WROVER_EAGLE-LTSPICE_C0402
EPD_C5: 0.1uF/50V; ESP32_WROVER_EAGLE-LTSPICE_C0402
EPD_CS: TPTP20R; TP20R
EPD_DC: TPTP20R; TP20R
EPD_RST: TPTP20R; TP20R
GND_1, GND_2: TPTP20R; TP20R
IC1: BD5229G-TR"; SOT95P280X125-5N
IC4: XC6220A331MR-G"; SOT95P280X120-5N
INT_RTC: TPTP20R; TP20R
J1: FH34SRJ-24S-0.5SH_99_"; FH34SRJ24S05SH99
J2: SAMACSYS_PARTS_USB4110-GF-ACU3D; SAMACSYS_PARTS_USB4110GFA
J3: QWIIC_RIGHT_ANGLE; JST04_1MM_RA
J4: 112A-TAAR-R03_ATTEND"; 112ATAARR03ATTEND
L1: 744043680IND_4828-WE-TPC_WRE; IND_4828-WE-TPC_WRE
MISO: TPTP20R; TP20R
MOSI: TPTP20R; TP20R
PFMF.050.1: ESP32C6_VARISTORCN1812; ESP32C6_VARISTOR_CT/CN1812
Q1, Q2: 20V/4.2A/52mΩ/1.4W; ESP32_WROVER_SPARKFUN-DISCRETESEMI_SOT23-3
Q3: SI1308EDL-T1-GE3""; SOT65P210X110-3N
R1, R1-PINH, R1-PINH1, R2-PINH, R2-PINH1, R4, R5, R6, R7, R8, R9, R10: 10K; ESP32_WROVER_EAGLE-LTSPICE_R0402
R1_BAT: 200; ESP32_WROVER_EAGLE-LTSPICE_R0402
R1_PWRUSB: 100K; ESP32_WROVER_EAGLE-LTSPICE_R0402
R2: 2.2; ESP32_WROVER_EAGLE-LTSPICE_R0402
R2-USB, R2-USB1: 5k1; ESP32_WROVER_EAGLE-LTSPICE_R0402
R2_BAT: 2K; ESP32_WROVER_EAGLE-LTSPICE_R0402
R3: 0.47; ESP32_WROVER_EAGLE-LTSPICE_R0402
RESET_BUTTON: BUTTON_CUSYOMV1"; MYBUTTON
RX: TPTP20R; TP20R
R_BOOT: 10K; ESP32_WROVER_EAGLE-LTSPICE_R0402
R_CAPACITOR: 15; ESP32_WROVER_EAGLE-LTSPICE_R0402
R_CHANGE: 10K; ESP32_WROVER_EAGLE-LTSPICE_R0402
R_CL1: 10K; ESP32_WROVER_EAGLE-LTSPICE_R0402
R_RESET: 10K; ESP32_WROVER_EAGLE-LTSPICE_R0402
SCK: TPTP20R; TP20R
SENSOR2: ESP32_WROVER_BME680_BME680"; ESP32_WROVER_BME680_PSON80P300X300X100-8N
SJ1: SJ""; SJ
TX: TPTP20R; TP20R
U1: W25Q512JVEIQ"; SON127P600X800X80-9N
U2: ESP32-C6-WROOM-1-N8"; XCVR_ESP32-C6-WROOM-1-N8
U3: DS3231SN#"; SOIC127P1032X265-16N
U4: MAX17048G+T10; SON50P200X200X80-9N
U5: ESP32_WROVER_SPARKFUN-IC-POWER_MCP73831"; ESP32_WROVER_SPARKFUN-IC-POWER_SOT23-5
VBAT: TPTP20R; TP20R
VBUS: TPTP20R; TP20R

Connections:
3V3: 3V3.TP, C1_BAT2.1, C3.+, C9.1, D7.2 (ANODE), IC1.2 (VDD), IC4.5 (VOUT), J3.2, J4.P4 (VDD), Q2.3 (D), R1.1, R1-PINH1.2, R2-PINH1.2, R5.2, R6.2, R7.2, R8.2, R9.2, R10.2, R_BOOT.1, R_CHANGE.1, R_CL1.1, R_RESET.1, U1.3 (!WP!(IO2)), U1.7 (!HOLD!/!RESET!(IO3)), U1.8 (VCC), U2.2 (3V3), U3.2 (VCC)
32KHZ: R2-PINH1.1, U2.9 (IO1), U3.1 (32KHZ)
DN: D1.4 (I/O2_2), J2.A7, J2.B7
DP: D1.6 (I/O1_2), J2.A6, J2.B6
EPD_3V3: C7.1, EPD_3V3.TP, EPD_C5.1, J1.15, J1.16, L1.2, Q2.2 (S)
EPD_3V3_C: EPD_3V3_C.TP, Q2.1 (G), R_CL1.2, U2.18 (IO20)
EPD_BUSY: EPD_BUSY.TP, J1.9, U2.26 (IO3)
EPD_CS: D6.1, EPD_CS.TP, J1.12, R9.1, U2.11 (IO10)
EPD_DC: EPD_DC.TP, J1.11, U2.5 (IO5)
EPD_RST: EPD_RST.TP, J1.10, U2.21 (IO23)
FLASH_CS: D9.1, R5.1, U1.1 (!CS), U2.12 (IO11)
GDR: J1.2, Q3.1 (G), R4.1
GND: BOOT_BUTTON.1, BOOT_BUTTON.2, C1.2, C1_BAT.2, C1_BAT1.2, C1_BAT2.2, C2.2, C2_BAT.2, C3.-, C4_USB.2, C5.2, C5_USB.2, C6.2, C7.2, C8.2, C9.2, C10.2, C10_SUPERCAP.1, CHANGE_BUTTON.1, CHANGE_BUTTON.2, C_DELAY.2, D1.2 (GND), D3.1 (K), D6.2, D8.2, D9.2, D10.2, D11.2, D12.2, EPD_C1.2, EPD_C2.2, EPD_C5.2, EPD_C6.2, EPD_C7.2, EPD_C8.2, EPD_C9.2, EPD_C10.2, EPD_C11.2, EPD_C12.2, GND_1.TP, GND_2.TP, IC1.3 (GND), IC4.2 (VSS), J1.8, J1.17, J1.MP1, J1.MP2, J2.A1, J2.A12, J2.B1, J2.B12, J2.MP1, J2.MP2, J2.MP3, J2.MP4, J3.1, J4.G1 (GND_1), J4.G2 (GND_2), J4.G3 (GND_3), J4.G4 (GND_4), J4.P6 (VSS), R1_PWRUSB.1, R2.1, R2-USB.2, R2-USB1.1, R2_BAT.1, R4.2, RESET_BUTTON.1, RESET_BUTTON.2, SENSOR2.1 (GND), SENSOR2.5 (SDO), SENSOR2.7 (GND), SJ1.1, U1.4 (GND), U1.9 (EXP), U2.1 (GND), U2.28 (GND), U2.29_1 (GND), U2.29_2 (GND), U2.29_3 (GND), U2.29_4 (GND), U2.29_5 (GND), U2.29_6 (GND), U2.29_7 (GND), U2.29_8 (GND), U2.29_9 (GND), U3.13 (GND), U4.1 (CTG), U4.4 (GND), U4.6 (QSTRT), U4.9 (EP), U5.2 (VSS)
GPIO8: R1.2, U2.10 (IO8)
I2C_PW: C1.1, C2.1, R1-PINH.2, R2-PINH.2, SENSOR2.2 (CSB), SENSOR2.6 (VDDIO), SENSOR2.8 (VDD), U2.17 (IO19)
INT_RTC: INT_RTC.TP, R1-PINH1.1, U2.8 (IO0), U3.3 (SQW/!INT)
IO/BOOT: BOOT_BUTTON.3, BOOT_BUTTON.4, C6.1, R_BOOT.2, U2.15 (IO9)
IO/CHANGE: C10.1, CHANGE_BUTTON.3, CHANGE_BUTTON.4, R_CHANGE.2, U2.23 (IO15)
MISO: D12.1, J4.P7 (DAT0), MISO.TP, R8.1, U1.2 (DO(IO1)), U2.27 (IO2)
MOSI: D11.1, J1.14, J4.P3 (CMD), MOSI.TP, R7.1, U1.5 (DI(IO0)), U2.7 (IO7)
unnamed: C1_BAT1.1, D2.1 (CATHODE), IC4.1 (VIN), IC4.3 (CE), Q1.2 (S)
unnamed: C_DELAY.1, IC1.5 (CT)
unnamed: J2.B5, R2-USB.1
unnamed: J2.A5, R2-USB1.2
unnamed: R1_BAT.1, U5.1 (STAT)
unnamed: CHG_LED.C, R1_BAT.2
unnamed: C4.1, D3.2 (A), D4.1 (K)
unnamed: R2_BAT.2, U5.5 (PROG)
unnamed: EPD_C1.1, J1.4
unnamed: EPD_C2.1, J1.5
unnamed: D7.1 (CATHODE), R_CAPACITOR.1
unnamed: EPD_C6.1, J1.18
unnamed: EPD_C7.1, J1.19
unnamed: EPD_C8.1, J1.20
unnamed: EPD_C10.1, J1.22
unnamed: EPD_C12.1, J1.24
PREVGH: D5.1 (K), EPD_C9.1, J1.21
PREVGL: D4.2 (A), EPD_C11.1, J1.23
RESE: J1.3, Q3.2 (S), R3.1
RESE': R2.2, R3.2, SJ1.2
RESET: C5.1, IC1.1 (VOUT), RESET_BUTTON.3, RESET_BUTTON.4, R_RESET.2, U2.3 (EN)
RTC_RST: U2.16 (IO18), U3.4 (!RST)
RX: RX.TP, U2.24 (RXD0/GPIO17)
SCK: D10.1, J1.13, J4.P5 (CLK), R6.1, SCK.TP, U1.6 (CLK), U2.6 (IO6)
SCL: J3.4, R2-PINH.1, SENSOR2.4 (SCK), U2.20 (IO22), U3.16 (SCL), U4.7 (SCL)
SDA: J3.3, R1-PINH.1, SENSOR2.3 (SDI), U2.19 (IO21), U3.15 (SDA), U4.8 (SDA)
SRC: C4.2, D5.2 (A), L1.1, Q3.3 (D)
SS_SD: D8.1, J4.P2 (CD/DAT3), R10.1, U2.4 (IO4)
TX: TX.TP, U2.25 (TXD0/GPIO16)
USB_D+: D1.1 (I/O1_1), U2.14 (IO13)
USB_D-: D1.3 (I/O2_1), U2.13 (IO12)
VBAT: C2_BAT.1, Q1.3 (D), U4.2 (CELL), U4.3 (VDD), U5.3 (VBAT), VBAT.TP
VBUS: C1_BAT.1, C4_USB.1, C5_USB.1, CHG_LED.A, D1.5 (VBUS), D2.2 (ANODE), PFMF.050.1.2, Q1.1 (G), R1_PWRUSB.2, U5.4 (VIN), VBUS.TP
VRTC: C8.1, C10_SUPERCAP.2, R_CAPACITOR.2, U3.14 (VBAT)
VUSB: J2.A4, J2.A9, J2.B4, J2.B9, PFMF.050.1.1

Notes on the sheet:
USB C connector & ESD protection
LDO Voltage Regulator
SD Card
ESP32 C6
Li-Po Battery Charging Controller
E-Paper Drive Circuit
Display Type Selector
E-Paper Display Header
EPD Power
Environmental Sensor BME688
Voltage Supervisor + Reset & Boot / IO Button
Battery Charge Level
RTC Module DS3231SN
Test Pads
Qwiic / Stemma QT
SPI ESD Protection Lines
External NOR Flash 64MB

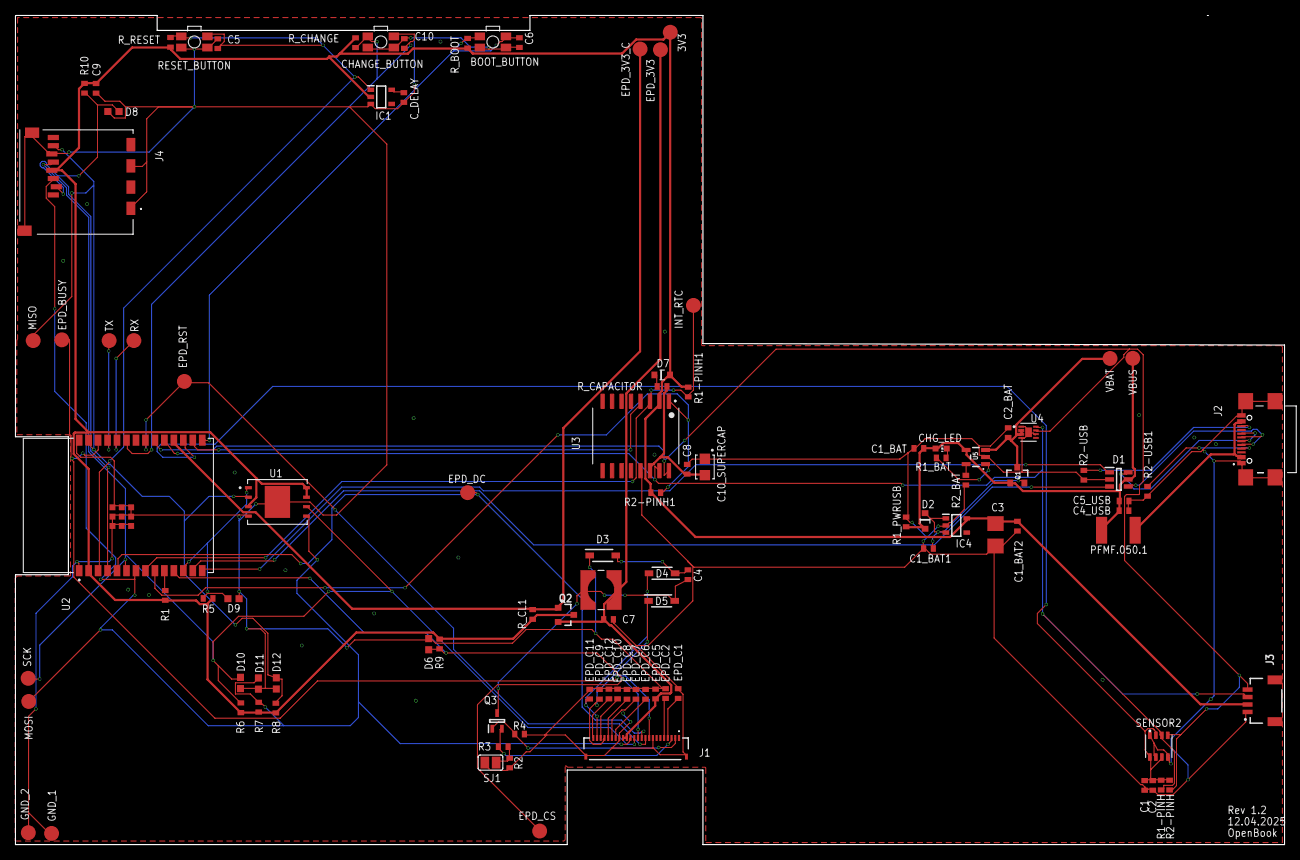
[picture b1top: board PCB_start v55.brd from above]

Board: 2 copper layers, 170.2 x 111.2 mm, 103 parts (0 on the bottom side), 55 nets.

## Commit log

2025-04-04 proj - to do README
2025-04-04 photo
2025-04-05 modif README
2025-04-05 added Exploded View
2025-04-12 Solved issues
